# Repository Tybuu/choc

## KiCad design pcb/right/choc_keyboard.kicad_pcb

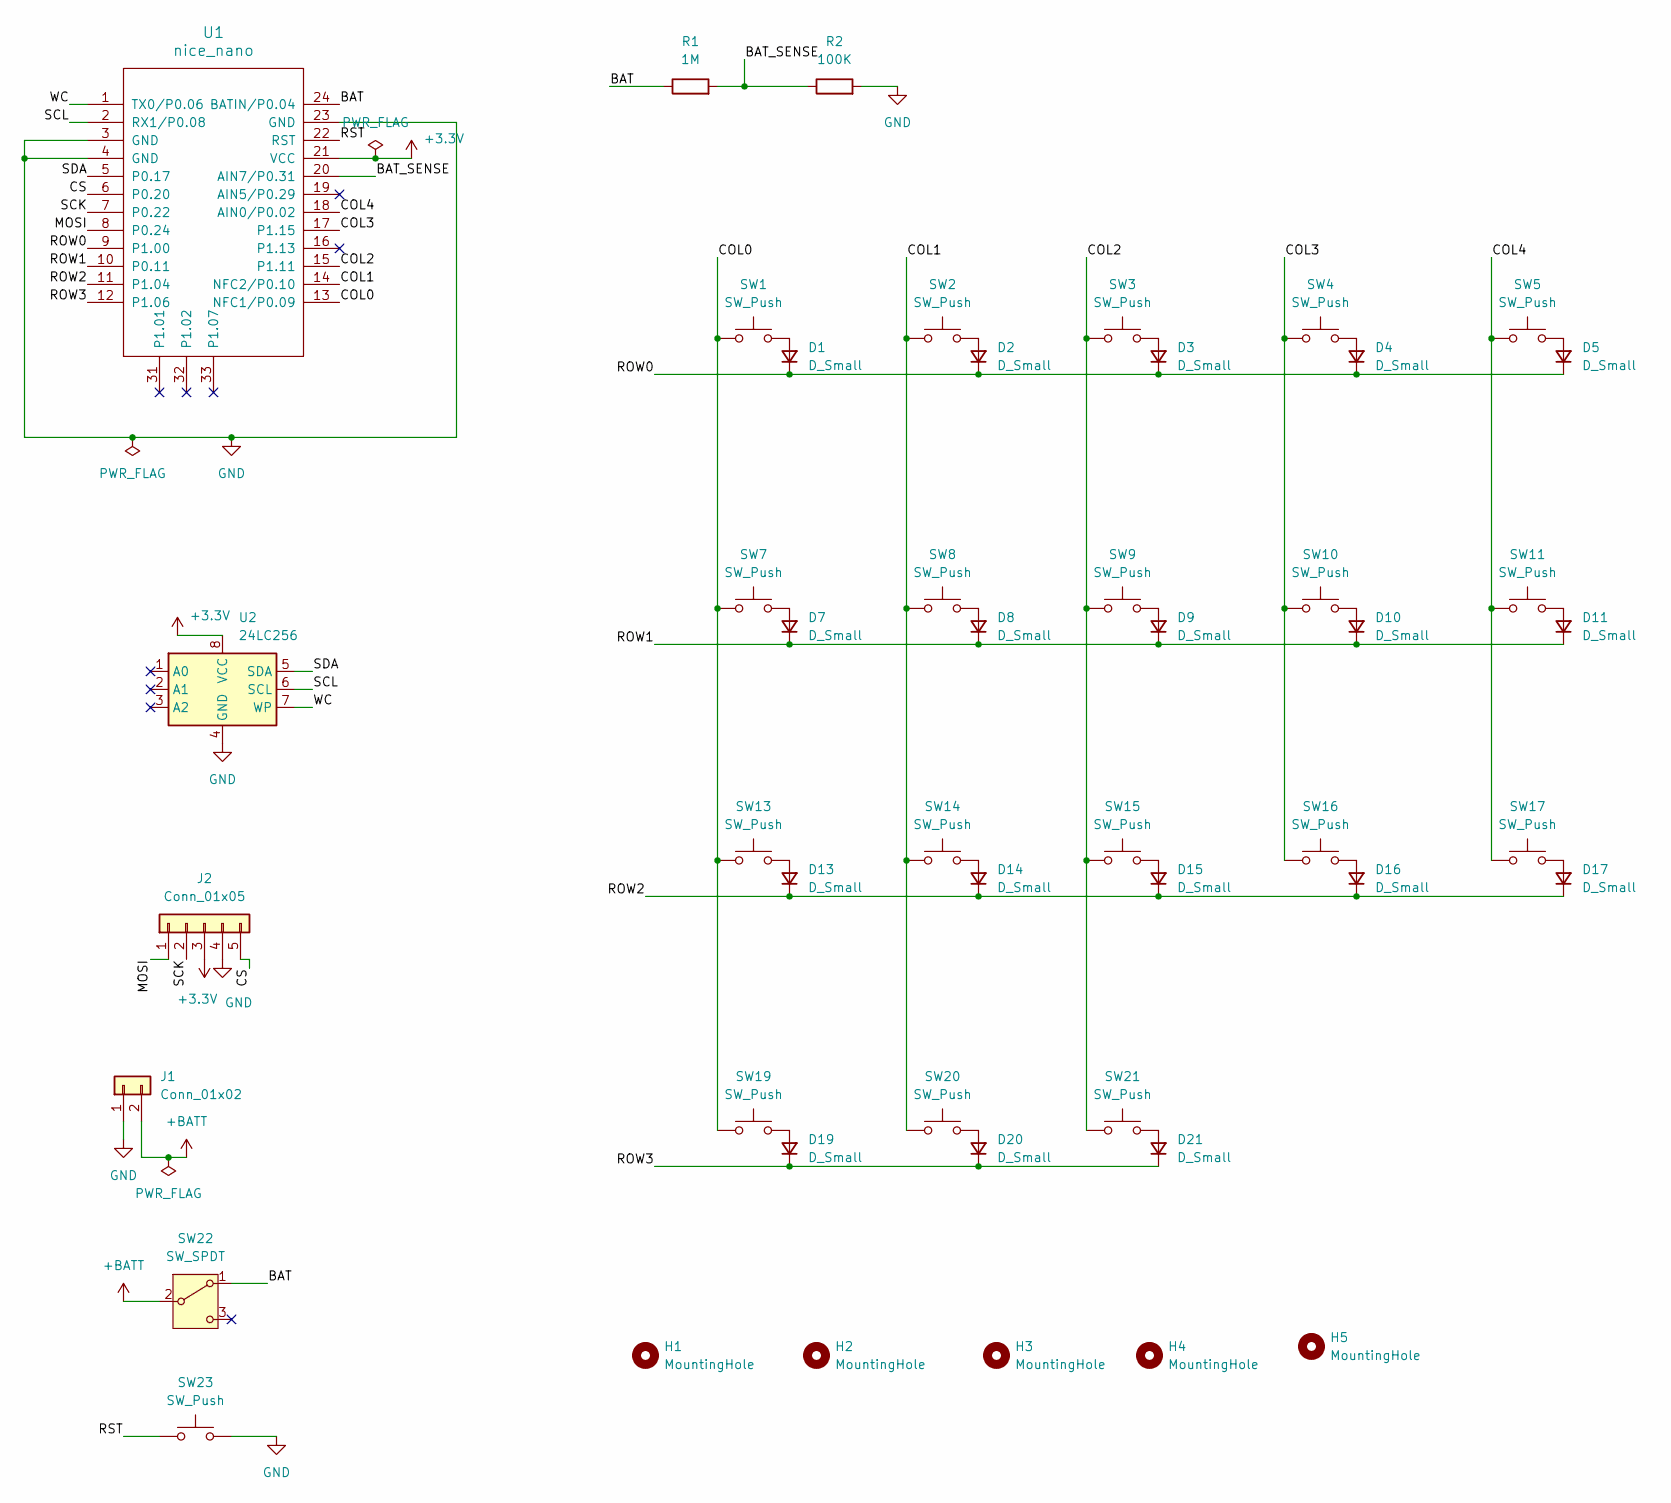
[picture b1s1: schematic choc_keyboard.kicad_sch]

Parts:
D1, D2, D3, D4, D5, D7, D8, D9, D10, D11, D13, D14, D15, D16, D17, D19, D20, D21: D_Small; D_SOD-123
H1, H2, H3, H4, H5: MountingHole; MountingHole_2.2mm_M2
J1: Conn_01x02; JST_PH_S2B-PH-K_1x02_P2.00mm_Horizontal
J2: Conn_01x05; PinSocket_1x05_P2.54mm_Vertical
R1: 1M; R_0603_1608Metric_Pad0.98x0.95mm_HandSolder
R2: 100K; R_0603_1608Metric_Pad0.98x0.95mm_HandSolder
SW1, SW2, SW3, SW4, SW5, SW7, SW8, SW9, SW10, SW11, SW13, SW14, SW15, SW16, SW17, SW19, SW20, SW21: SW_Push; SW_Hotswap_Kailh_Choc_V1V2_1.1
SW22: SW_SPDT; SW_SPDT_PCM12
SW23: SW_Push; Panasonic_EVQPUL_EVQPUC
U1: nice_nano
U2: 24LC256; TSSOP-8_4.4x3mm_P0.65mm

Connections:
+3.3V: J2.3, U1.21 (VCC), U2.8 (VCC)
+BATT: J1.2, SW22.2 (B)
/BAT: R1.1, SW22.1 (A), U1.24 (BATIN/P0.04)
/BAT_SENSE: R1.2, R2.1, U1.20 (AIN7/P0.31)
/COL0: SW1.1, SW7.1, SW13.1, SW19.1, U1.13 (NFC1/P0.09)
/COL1: SW2.1, SW8.1, SW14.1, SW20.1, U1.14 (NFC2/P0.10)
/COL2: SW3.1, SW9.1, SW15.1, SW21.1, U1.15 (P1.11)
/COL3: SW4.1, SW10.1, SW16.1, U1.17 (P1.15)
/COL4: SW5.1, SW11.1, SW17.1, U1.18 (AIN0/P0.02)
/CS: J2.5, U1.6 (P0.20)
/MOSI: J2.1, U1.8 (P0.24)
/ROW0: D1.1 (K), D2.1 (K), D3.1 (K), D4.1 (K), D5.1 (K), U1.9 (P1.00)
/ROW1: D7.1 (K), D8.1 (K), D9.1 (K), D10.1 (K), D11.1 (K), U1.10 (P0.11)
/ROW2: D13.1 (K), D14.1 (K), D15.1 (K), D16.1 (K), D17.1 (K), U1.11 (P1.04)
/ROW3: D19.1 (K), D20.1 (K), D21.1 (K), U1.12 (P1.06)
/RST: SW23.1, U1.22 (RST)
/SCK: J2.2, U1.7 (P0.22)
/SCL: U1.2 (RX1/P0.08), U2.6 (SCL)
/SDA: U1.5 (P0.17), U2.5 (SDA)
/WC: U1.1 (TX0/P0.06), U2.7 (WP)
GND: J1.1, J2.4, R2.2, SW23.2, U1.3 (GND), U1.4 (GND), U1.23 (GND), U2.4 (GND)
unnamed: D1.2 (A), SW1.2
unnamed: D2.2 (A), SW2.2
unnamed: D3.2 (A), SW3.2
unnamed: D4.2 (A), SW4.2
unnamed: D5.2 (A), SW5.2
unnamed: D7.2 (A), SW7.2
unnamed: D8.2 (A), SW8.2
unnamed: D9.2 (A), SW9.2
unnamed: D10.2 (A), SW10.2
unnamed: D11.2 (A), SW11.2
unnamed: D13.2 (A), SW13.2
unnamed: D14.2 (A), SW14.2
unnamed: D15.2 (A), SW15.2
unnamed: D16.2 (A), SW16.2
unnamed: D17.2 (A), SW17.2
unnamed: D19.2 (A), SW19.2
unnamed: D20.2 (A), SW20.2
unnamed: D21.2 (A), SW21.2

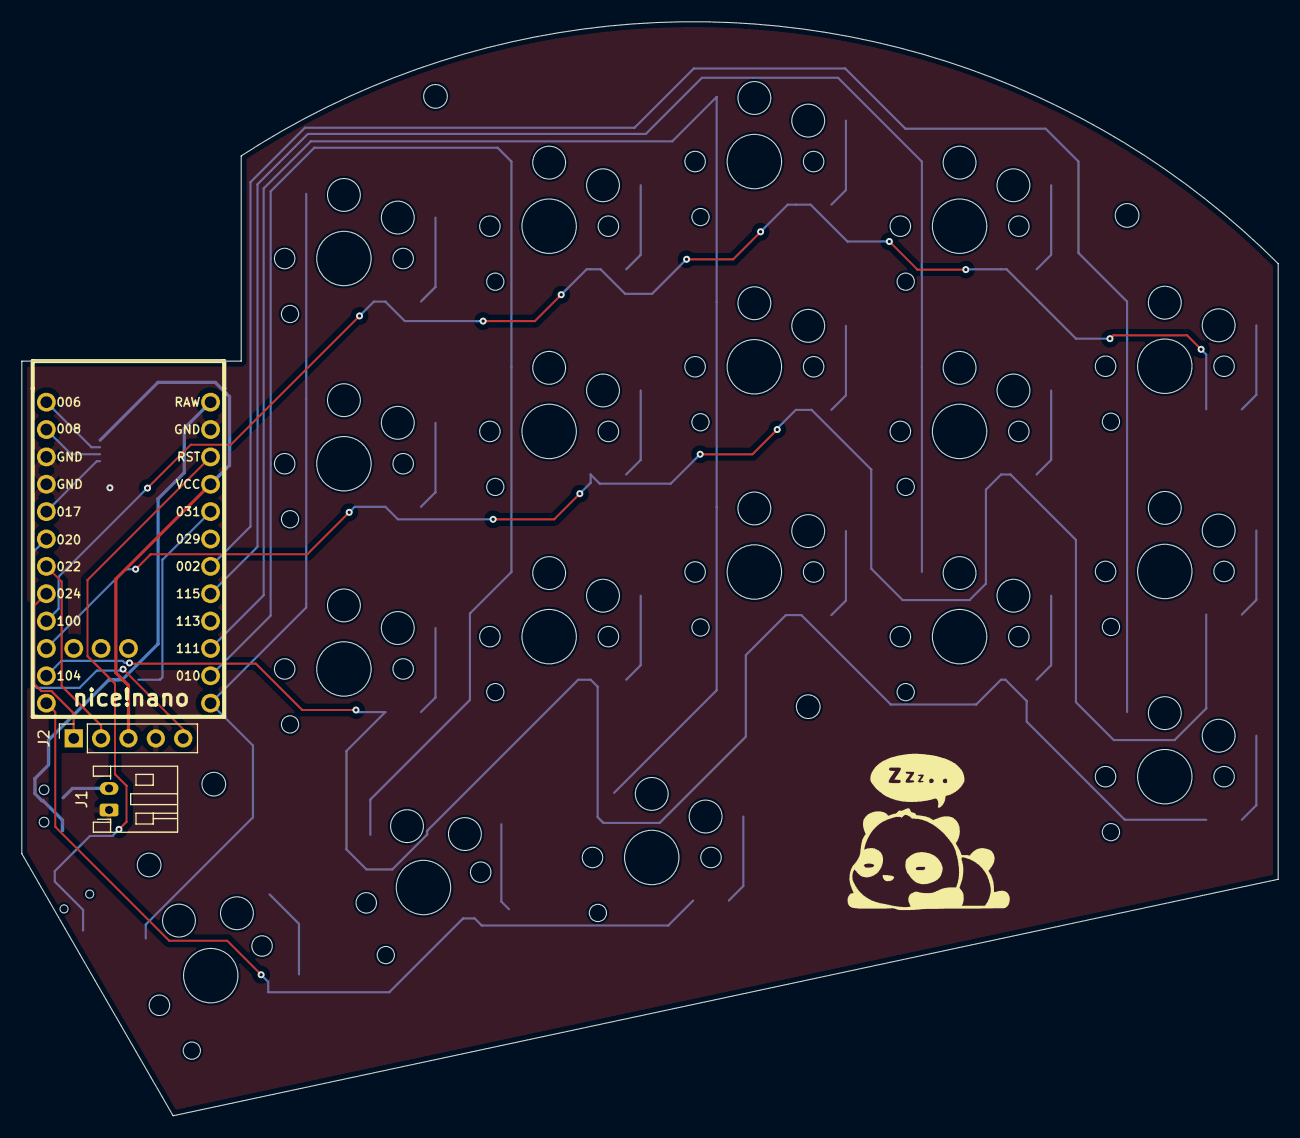
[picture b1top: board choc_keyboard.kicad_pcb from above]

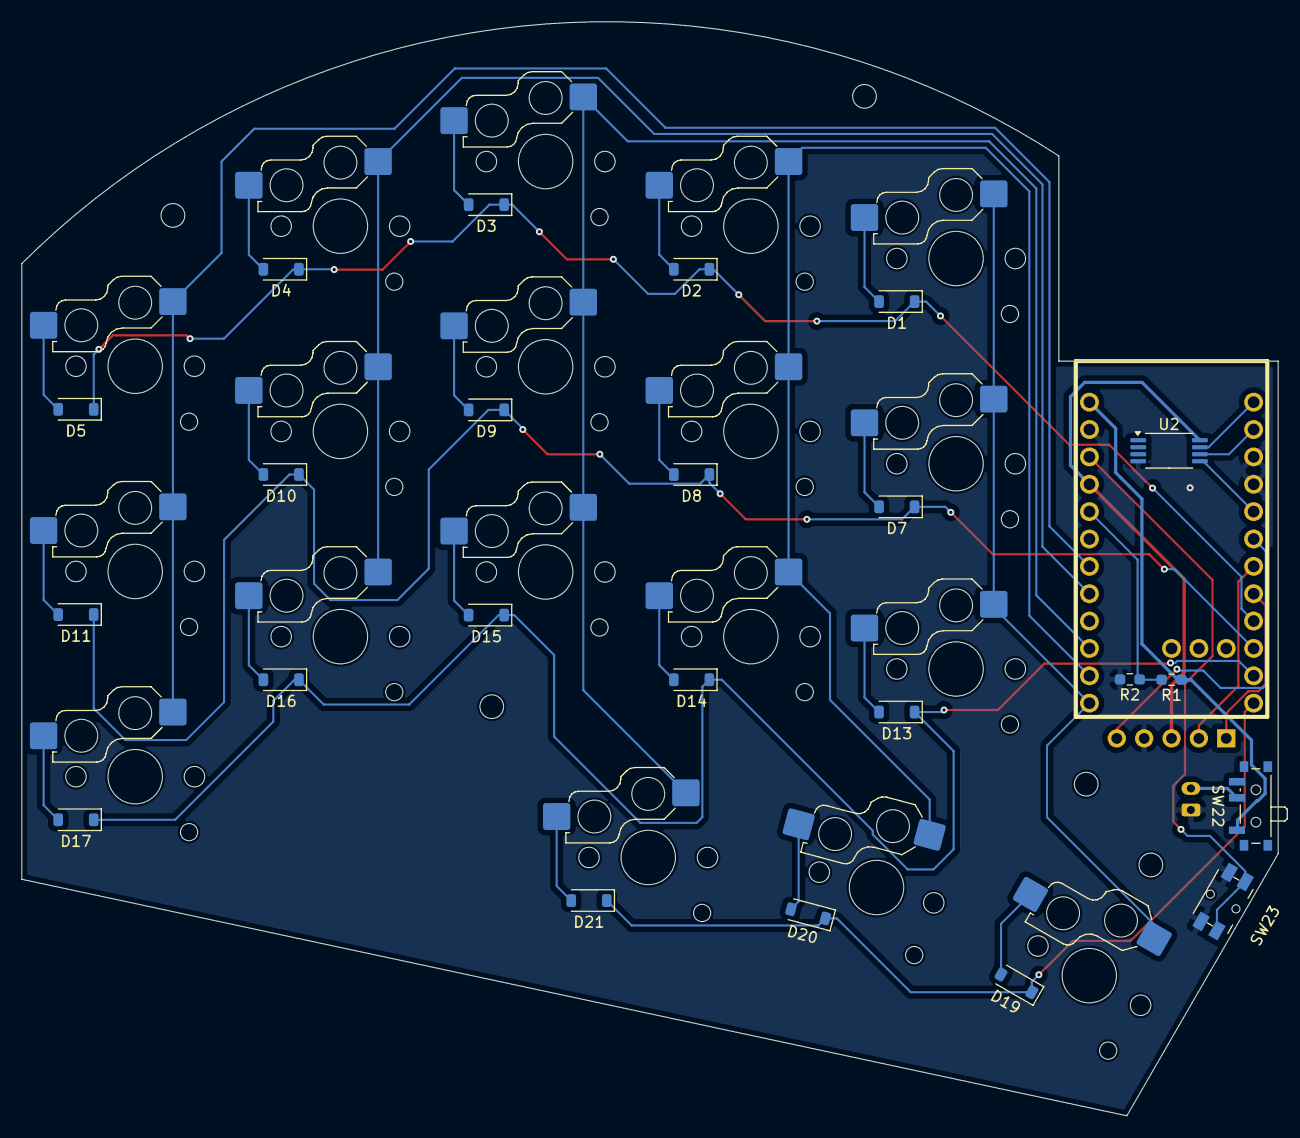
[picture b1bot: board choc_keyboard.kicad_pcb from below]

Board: 2 copper layers, 116.6 x 101.5 mm, 49 parts (23 on the bottom side), 39 nets.

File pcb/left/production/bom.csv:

Designator,Footprint,Quantity,Value,LCSC Part #
"D1, D10, D11, D13, D14, D15, D16, D17, D19, D2, D20, D21, D3, D4, D5, D7, D8, D9",D_SOD-123,18,D_Small,
J1,JST_PH_S2B-PH-K_1x02_P2.00mm_Horizontal,1,Conn_01x02,
J2,PinSocket_1x05_P2.54mm_Vertical,1,Conn_01x05,
R1,0603,1,1M,
R2,0603,1,100K,
"SW1, SW10, SW11, SW13, SW14, SW15, SW16, SW17, SW19, SW2, SW20, SW21, SW3, SW4, SW5, SW7, SW8, SW9",SW_Hotswap_Kailh_Choc_V1V2_1.1,18,SW_Push,
SW22,SW_SPDT_PCM12,1,SW_SPDT,
SW23,Panasonic_EVQPUL_EVQPUC,1,SW_Push,
U1,nice_nano,1,nice_nano,
U2,TSSOP-8_4.4x3mm_P0.65mm,1,24LC256,

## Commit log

2024-12-23 finished pcbs
2025-01-08 starting code
2025-01-10 got one key ble working
2025-01-10 got left side somewhat working
2025-01-10 got nkro report working
2025-01-14 finished basic config for keyboards to communicate with one another through ble
2025-01-17 fixed matrix sleeping before debouncer stabalizes
2025-01-18 switched to port interrupts from gpiote interrupts for matrix
2025-03-24 config update
2025-03-28 remove sd references from central and link
2025-03-28 made central carry less references
2025-03-28 changed .gitignore
2025-03-28 actually changed gitignore
2025-03-28 removed firmware outputs
2025-03-28 changed makefile
2025-03-28 starting on dual
2025-03-29 first implementation of dongle
